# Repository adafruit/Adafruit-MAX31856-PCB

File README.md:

## Adafruit MAX31856 PCB

<a href="http://www.adafruit.com/products/3263"><br/>
Click here to purchase one from the Adafruit shop</a>

PCB files for the Adafruit MAX31856 Thermocouple Amplifier Breakout. Format is EagleCAD schematic and board layout
* https://www.adafruit.com/product/3263

### Description

Thermocouples are very sensitive, requiring a good amplifier with a cold-compensation reference, as well as calculations to handle any non-linearities. For a long time we've suggested our MAX31855K breakout, which works great but is only for K-type thermocouples. Now we're happy to offer a great new thermocouple amplifier/converter that can handle just about any type of thermocouple, and even has the ability to give you notification when the temperature goes out of range, or a fault occurs. Very fancy!

This converter communicates over 4-wire SPI and can interface with any K, J, N, R, S, T, E, or B type thermocouple.

This breakout does everything for you, and can be easily interfaced with any microcontroller, even one without an analog input. This breakout board has the chip itself, a 3.3V regulator and level shifting circuitry, all assembled and tested. Comes with a 2 pin terminal block (for connecting to the thermocouple) and pin header (to plug into any breadboard or perfboard). We even added inline resistors and a filter capacitor on-board for better stability, as recommended by Maxim. Goes great with our 1m K-type thermocouple or any other thermocouple, really!

### License

Adafruit invests time and resources providing this open source design, please support Adafruit and open-source hardware by purchasing products from [Adafruit](https://www.adafruit.com)!

Designed by Limor Fried/Ladyada for Adafruit Industries.

Creative Commons Attribution/Share-Alike, all text above must be included in any redistribution. See license.txt for additional details.

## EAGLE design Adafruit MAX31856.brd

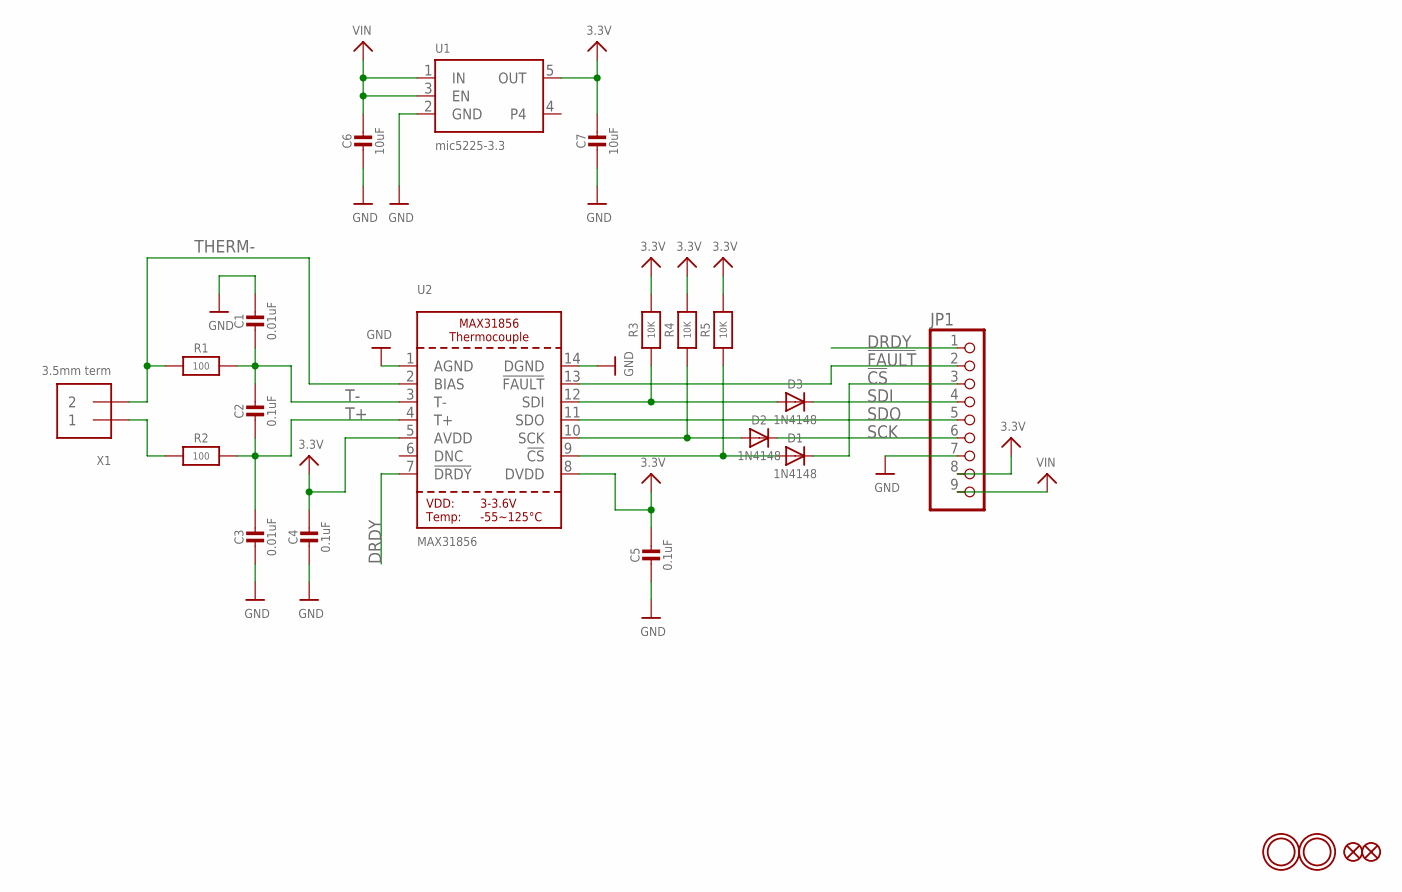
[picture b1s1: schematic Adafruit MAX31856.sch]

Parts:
C1: 0.01uF; 0805_10MGAP
C2, C4, C5: 0.1uF; 0805-NO
C3: 0.01uF; 0805-NO
C6, C7: 10uF; 0805-NO
D1, D2, D3: 1N4148; SOD-323
FID1, FID2: FIDUCIAL""; FIDUCIAL_1MM
JP1: HEADER-1X970MIL; 1X09_ROUND_70
R1, R2: 100; 0805-NO
R3, R4, R5: 10K; 0805-NO
U1: mic5225-3.3; SOT23-5
U2: MAX31856; TSSOP14
U$13, U$14: MOUNTINGHOLE2.5; MOUNTINGHOLE_2.5_PLATED
X1: 3.5mm term; TERMBLOCK_1X2-3.5MM

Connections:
3.3V: C4.1, C5.1, C7.1, JP1.8, R3.2, R4.2, R5.2, U1.5 (OUT), U2.5 (AVDD), U2.8 (DVDD)
!CS: D1.C, JP1.3
!CS_3V: D1.A, R5.1, U2.9 (!CS)
!FAULT: JP1.2, U2.13 (!FAULT)
DRDY: JP1.1, U2.7 (!DRDY)
GND: C1.1, C3.2, C4.2, C5.2, C6.2, C7.2, JP1.7, U1.2 (GND), U2.1 (AGND), U2.14 (DGND)
SCK: D2.C, JP1.6
SCK_3V: D2.A, R4.1, U2.10 (SCK)
SDI: D3.C, JP1.4
SDO: JP1.5, U2.11 (SDO)
SDO_3V: D3.A, R3.1, U2.12 (SDI)
T+: C2.2, C3.1, R2.2, U2.4 (T+)
T-: C1.2, C2.1, R1.2, U2.3 (T-)
THERM+: R2.1, X1.1
THERM-: R1.1, U2.2 (BIAS), X1.2
VIN: C6.1, JP1.9, U1.1 (IN), U1.3 (EN)

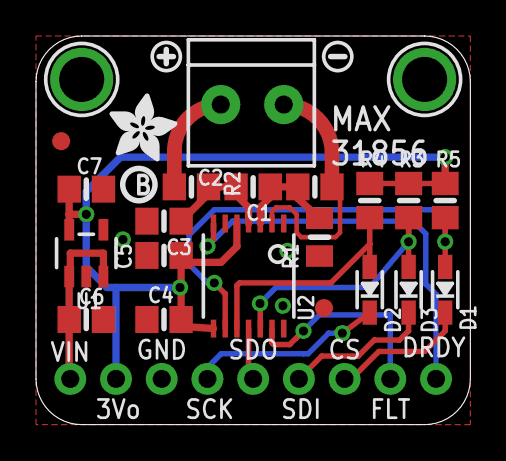
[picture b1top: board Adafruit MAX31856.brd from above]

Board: 2 copper layers, 24.1 x 21.6 mm, 28 parts (1 on the bottom side), 16 nets.

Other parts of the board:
U$1: PCBFEAT-REV-040
U$23: SYMBOL_PLUS
U$24: SYMBOL_MINUS
U$25: ADAFRUIT_3.5MM
U$26: ADAFRUIT_TEXT_20MM

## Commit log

2016-09-22 init
2023-08-20 Add KiCad symbol, footprint, and 3d model

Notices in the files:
parts and their libraries:
microbuilder: This work is placed in the public domain, and may be freely used for commercial and non-commercial work with the following conditions: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
